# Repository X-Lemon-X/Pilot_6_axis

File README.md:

# 6 axis remote Controler
- Works over Wi-Fi ( sends constant length ASCI data frame)
- Up to 6 networks saved (with priority from  1 to 6)
- All settings of the Rc can be changed on a configuration website
- Controled inertia of the joysticks and signal values of the joystick coordinates
- Veriable signal refresh rate up to 200Hz
- Auto zero positioning (no more robots moving in slow speed without touching the pilot)
- USB-C charged!
- two 3-DOF joysticks
- 10 buttons (2 of which are on Joy Sticks)
- Integrated LCD
- The RC remembers settings so no need to set it up every time or reprogram it.

## The repo supports demo pc keyboard version of the RC 
 Pc keyboard version for RC without the need for the hardware.
 
 ```bash
  python3 -m venv .venv
  python3 -m pip -r requirements.txt
  source .venv/bin/activate
  python3 pilot_6axis/pilot_6axis/keyboard_rc.py -i IP_ADDRESS -p PORT -f FREQUENCY -v JOYSTICK_VALUE
 ```
for help
```bash
  python3 pilot_6axis/pilot_6axis/keyboard_rc.py
 ```

## To build and run ros package
```bash
  colcon build --packages-select pilot_6axis
  source install/setup.bash 
  ros2 run pilot_6axis rc_node
```

## Data frame
 Consist of 18 elements separated by ':'.
Depending on the settings int_Joystick_(left/right)_(MMin/MMax) value returned by joystick will vary. This setting values should be between -9999<=x<=9999 or 0<=x<=99999 or the data frame length won't be constant, for buttons: 1-pressed 0-not pressed.
```bash
 Example: "$Rc:  340:   200:   12:1:  500:-2045: 2045:1:1:1:0:1:1:0:1:0:#\r"
```

 1. control beginning "$Rc"
 2. joystick_left_x   (5-characters) 
 3. joystick_left_y   (5-characters)
 4. joystick_left_z   (5-characters)
 5. joystick_left_btn  (1-character)
 6. joystick_right_x   (5-characters)
 7. joystick_right_y   (5-characters)
 8. joystick_right_z   (5-characters)
 9. joystick_right_btn  (1-character)
 10. btn_1  (1-character)
 11. btn_2  (1-character)
 12. btn_3  (1-character)
 13. btn_4  (1-character)
 14. btn_5  (1-character)
 15. btn_6  (1-character)
 16. btn_7  (1-character)
 17. btn_8  (1-character)
 18. control end "#\r"

## How to use
### Setup
  1. Enable setup mode by pressing and holding the most centeral button 4 or 5 when turning the Rc On (doesn't matter which one).
  2. Connect to the Rc Wi-Fi network that is displayed on  the LCD.
  3. Open web browser and go to url displayed on the LCD.
  4. Set up the settings of the Rc and press save buttons on the bottom of the page. This will redirect you to the page where you will see if settings were saved. If you made some error it will be shown here.
  5. To leave setup mode shut down the Rc and turn it on again.
  6. Now the Rc will connect to the network with the highest priority that is available. If it can't connect to any of the saved networks it will keep trying to connect to them. If the Rc is connected to the network it will display the IP address on the LCD and show Connected status.
  7. Now setup is done and you can use the Rc.
## Settings list:
#### General Settings
  - **Joystick left MMin** -> minimum value of the left joystick x, y, z axis on the min of the range 
  - **Joystick left MMax** -> maximum value of the left joystick x, y, z axis on the max of the range
  - **Joystick left filer** -> inertia of the left joystick (0-1), the higher inertia the response of the joystick value will be faster.
  - **Joystick right MMin** -> minimum value of the right joystick x, y, z axis on the min of the range
  - **Joystick right MMax** -> maximum value of the right joystick x, y, z axis on the max of the range
  - **Joystick right filer** -> inertia of the right joystick (0-1)
  - **WIFI SSID** => SSID of the wifi network created by the RC in setup mode.
  - **WIFI PASSWORD** => password of the wifi network made by the RC in setup mode
  - **Update frequency** => frequency of sending data frame
  - **Target IP** => IP address to which the RC will send data frame
  - **Host Port** => port to which the RC will send data frame

#### WIFI target networks
  - **Wifi [number 1-6] : Seed** => SSID of the wifi network (where number means priority from 1 to 6)
  - **Wifi [number 1-6] : Password** => Password of the wifi network

## Required component list

### Component Images

  | Component | Photo | Component | Photo |
  |-----------|-------|-----------|-------|
  | PCB (order from JLCPCB) |  | Joystick 4-axis JH-D400B-M4 |  |
  | Toggle switch 6mm MTS-103 |  | Monostable switches 12mm PBS-33B |  |
  | Li-ion battery 3.7V 4000mAh |  | LCD 1.3" 128x64 OLED SSD1306 |  |
  | Antena 2.4GHz 3dBi WiFi RP-SMA |  | M3 6mm hex socket flat countersunk |  |
  | M3 heated insert M3xL3xOD4.2 |  | M3 5mm hex socket cylindrical |  |

### Component list 

  | Component Name                                   | Parts Count | Description                                              |
  |--------------------------------------------------|-------------|----------------------------------------------------------|
  | Joystick 4-axis JH-D400B-M4                      | 2           | 3-DOF joysticks for axis control                        |
  | Toggle switch 6mm MTS-103                        | 1           | Main toggle switch for power or mode selection           |
  | Monostable switches 12mm PBS-33B                 | 8           | Momentary push buttons for user input                   |
  | Li-ion battery 606090 3.7V 4000mAh               | 1           | Rechargeable battery for power supply                    |
  | LCD 1.3" 128x64 OLED SSD1306                     | 1           | Display for status and configuration                     |
  | Antena 2.4GHz 3dB WiFi 2.4GHz RP-SMA             | 1           | External Wi-Fi antenna for wireless communication        |
  | M3 6mm hex socket flat countersunk screws        | 14          | Screws for assembling the enclosure                      |
  | M3 heated insert M3xL3xOD4.2                     | 19          | Threaded inserts for secure screw mounting               |
  | M3 5mm hex socket cylindrical screws             | 4           | Additional screws for assembly                           |
  | PCB (order from JLCPCB)                          | 1           | Main circuit board for the controller                    |
  | BOM Components (see BOM file)                    | -           | All other electronic components (resistors, ICs, etc.)   |

- BOM file "Electric schematic/Pilot6Axis/jlcpcb/production_files/BOM-Pilot6Axis.csv"
- JLCB gerber files "Electric schematic/Pilot6Axis/jlcpcb/production_files/GERBER-Pilot6Axis.zip"

## How to assembly
  You figure it out.

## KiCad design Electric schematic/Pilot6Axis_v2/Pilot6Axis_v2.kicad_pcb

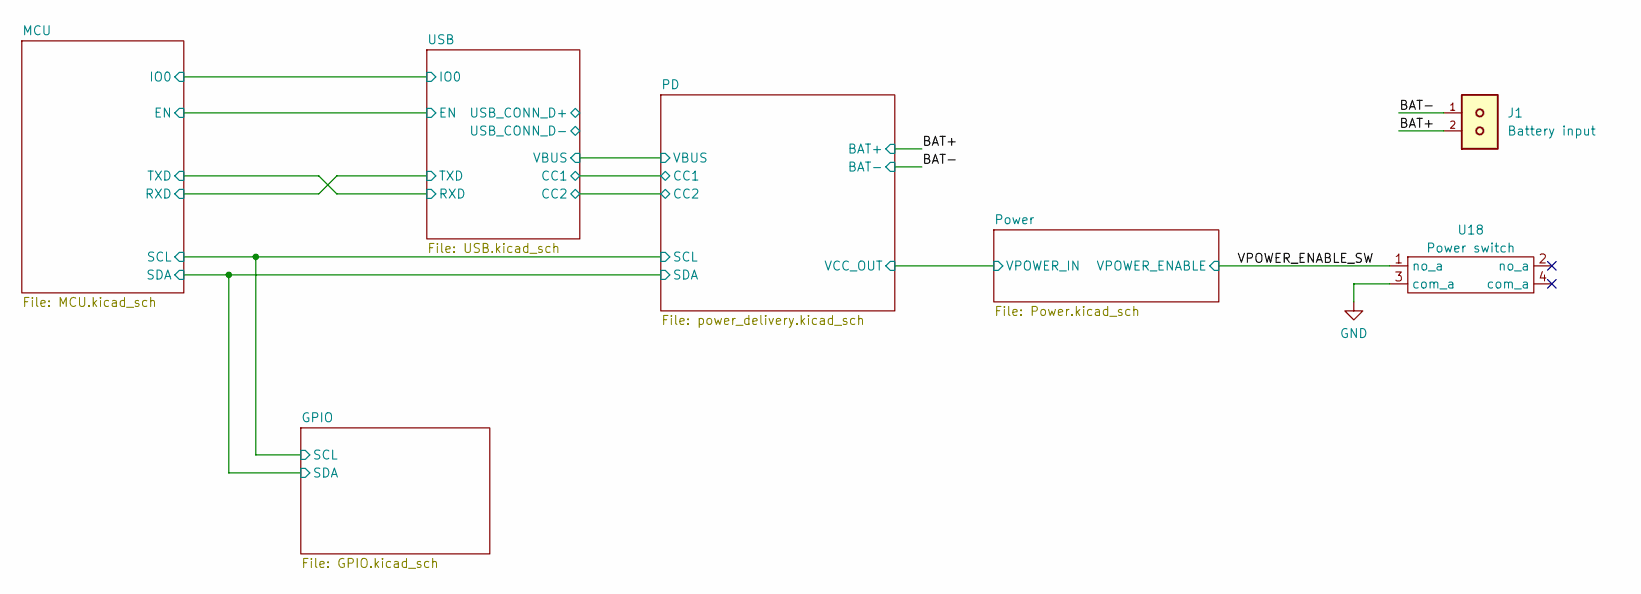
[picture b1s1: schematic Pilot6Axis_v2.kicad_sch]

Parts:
J1: Battery input; JST_PH_B2B-PH-K_1x02_P2.00mm_Vertical
U18: Power switch; ts-1212f

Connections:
/BAT+: J1.2; also elsewhere on the board
/VPOWER_ENABLE_SW: U18.1 (no_a); also elsewhere on the board
GND: J1.1, U18.3 (com_a); also elsewhere on the board

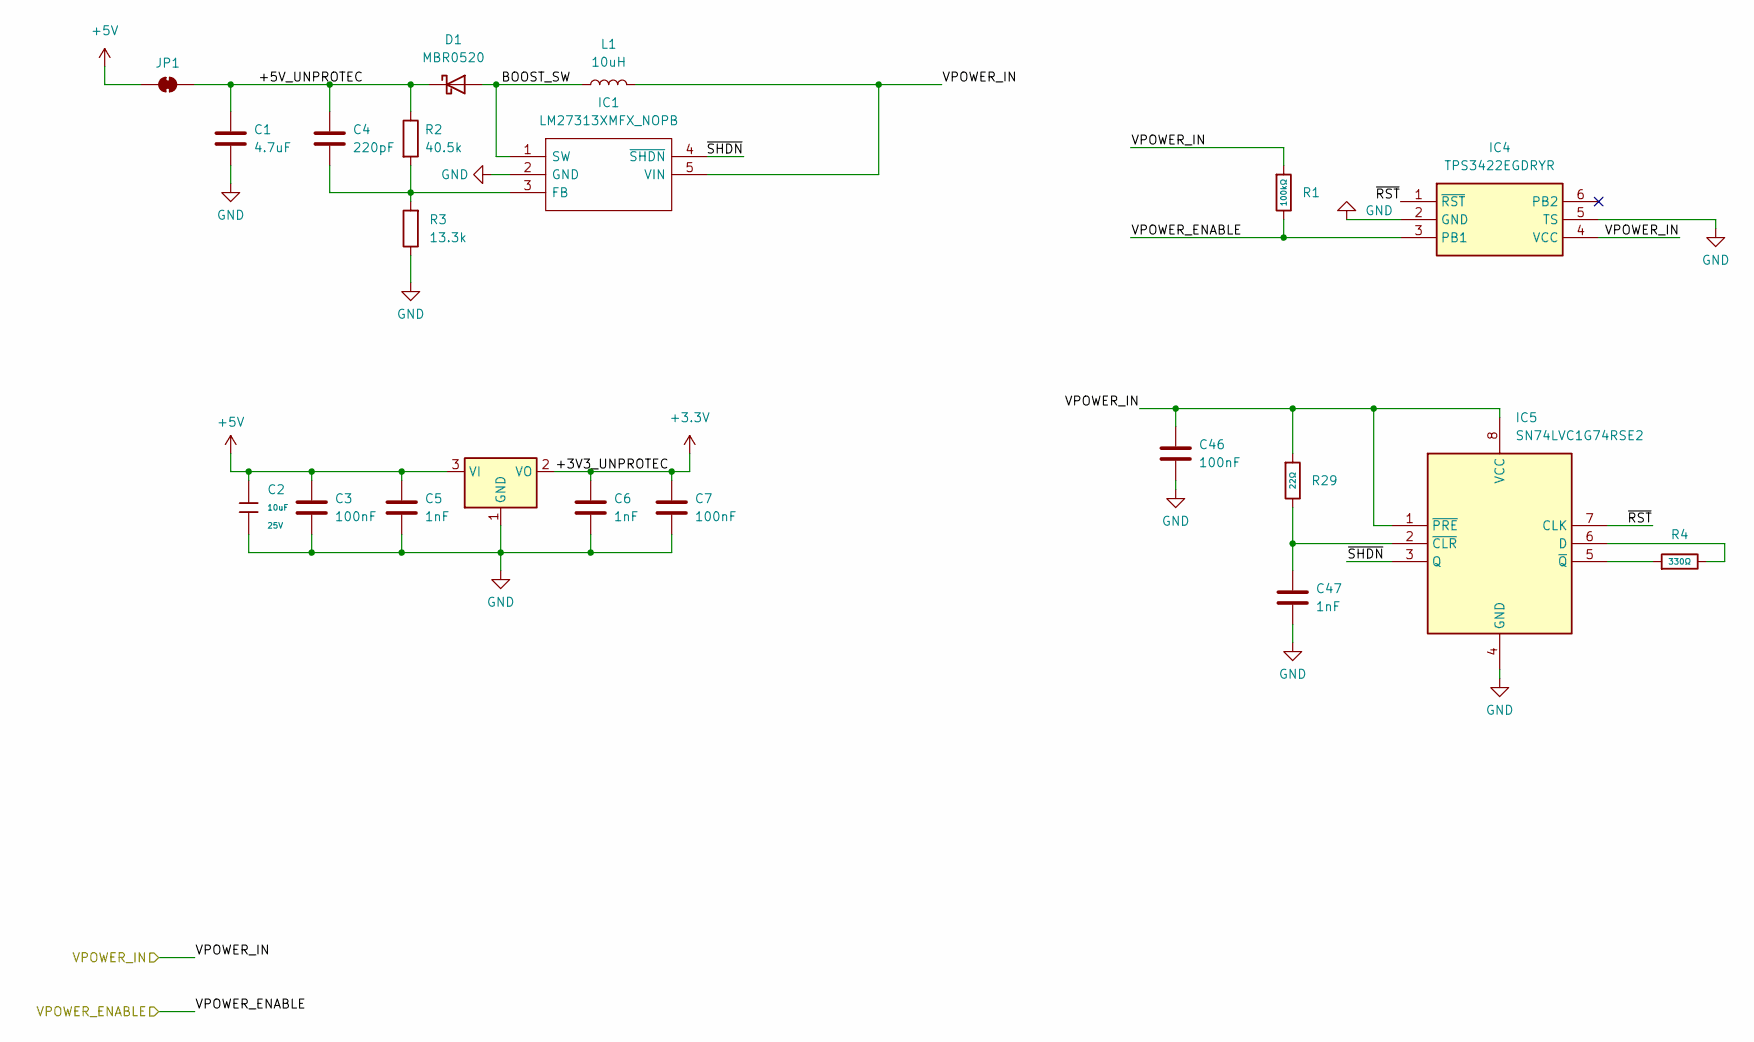
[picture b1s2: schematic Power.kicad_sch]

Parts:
C1: 4.7uF; C_0603_1608Metric; LCSC C19666
C2: 10uF; C_0603; Voltage Rated 25V; Tolerance ±20%; Part CL10A106MA8NRNC; LCSC C96446
C3, C7, C46: 100nF; C_0603_1608Metric; LCSC C14663
C4: 220pF; C_0603_1608Metric; LCSC C1603
C5, C6, C47: 1nF; C_0603_1608Metric; LCSC C1588
D1: MBR0520; D_0603_1608Metric; LCSC C2858712
IC1: LM27313XMFX_NOPB; SOT-23-5; Manufacturer_Part_Number LM27313XMFX/NOPB; Mouser Part Number 926-LM27313XMFX/NOPB
IC4: TPS3422EGDRYR; DRY_R-PUSON-N6_; Manufacturer_Part_Number TPS3422EGDRYR; Mouser Part Number 595-TPS3422EGDRYR
IC5: SN74LVC1G74RSE2; Manufacturer_Part_Number SN74LVC1G74RSE2; Mouser Part Number 595-SN74LVC1G74RSE2
JP1: SolderJumper_2_Bridged; SolderJumper-2_P1.3mm_Open_TrianglePad1.0x1.5mm
L1: 10uH; L_Cenker_CKCS4018; LCSC C1035
R1: 100kΩ; R_0603; Overload Voltage (Max) 75V; Tolerance ±1%; Part 0603WAF1003T5E; LCSC C25803
R2: 40.5k; R_0603_1608Metric; LCSC C12447
R3: 13.3k; R_0603_1608Metric; LCSC C25952
R4: 330Ω; R_0603; Overload Voltage (Max) 75V; Tolerance ±1%; Part 0603WAF3300T5E; LCSC C23138
R29: 22Ω; R_0603; Overload Voltage (Max) 75V; Tolerance ±1%; Part 0603WAF220JT5E; LCSC C23345
U1: AMS1117-3.3; SOT-223-3_TabPin2; LCSC C6186

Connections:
+3.3V: C6.1, C7.1, U1.2 (VO); also elsewhere on the board
+5V: C2.1, C3.1, C5.1, JP1.1 (A), U1.3 (VI); also elsewhere on the board
/PD/VCC_OUT: C46.1, IC1.5 (VIN), IC4.4 (VCC), IC5.1 (~PRE), IC5.8 (VCC), L1.2, R1.1, R29.1; also elsewhere on the board
/Power/+5V_UNPROTEC: C1.1, C4.2, D1.1 (K), JP1.2 (B), R2.1
/Power/BOOST_SW: D1.2 (A), IC1.1 (SW), L1.1
/Power/~RST: IC4.1 (~RST), IC5.7 (CLK)
/Power/~SHDN: IC1.4 (~SHDN), IC5.3 (Q)
/VPOWER_ENABLE_SW: IC4.3 (PB1), R1.2; also elsewhere on the board
GND: C1.2, C2.2, C3.2, C5.2, C6.2, C7.2, C46.2, C47.2, IC1.2 (GND), IC4.2 (GND), IC4.5 (TS), IC5.4 (GND), R3.1, U1.1 (GND); also elsewhere on the board
unnamed: C4.1, IC1.3 (FB), R2.2, R3.2
unnamed: IC5.6 (D), R4.2
unnamed: C47.1, IC5.2 (~CLR), R29.2
unnamed: IC5.5 (~Q), R4.1

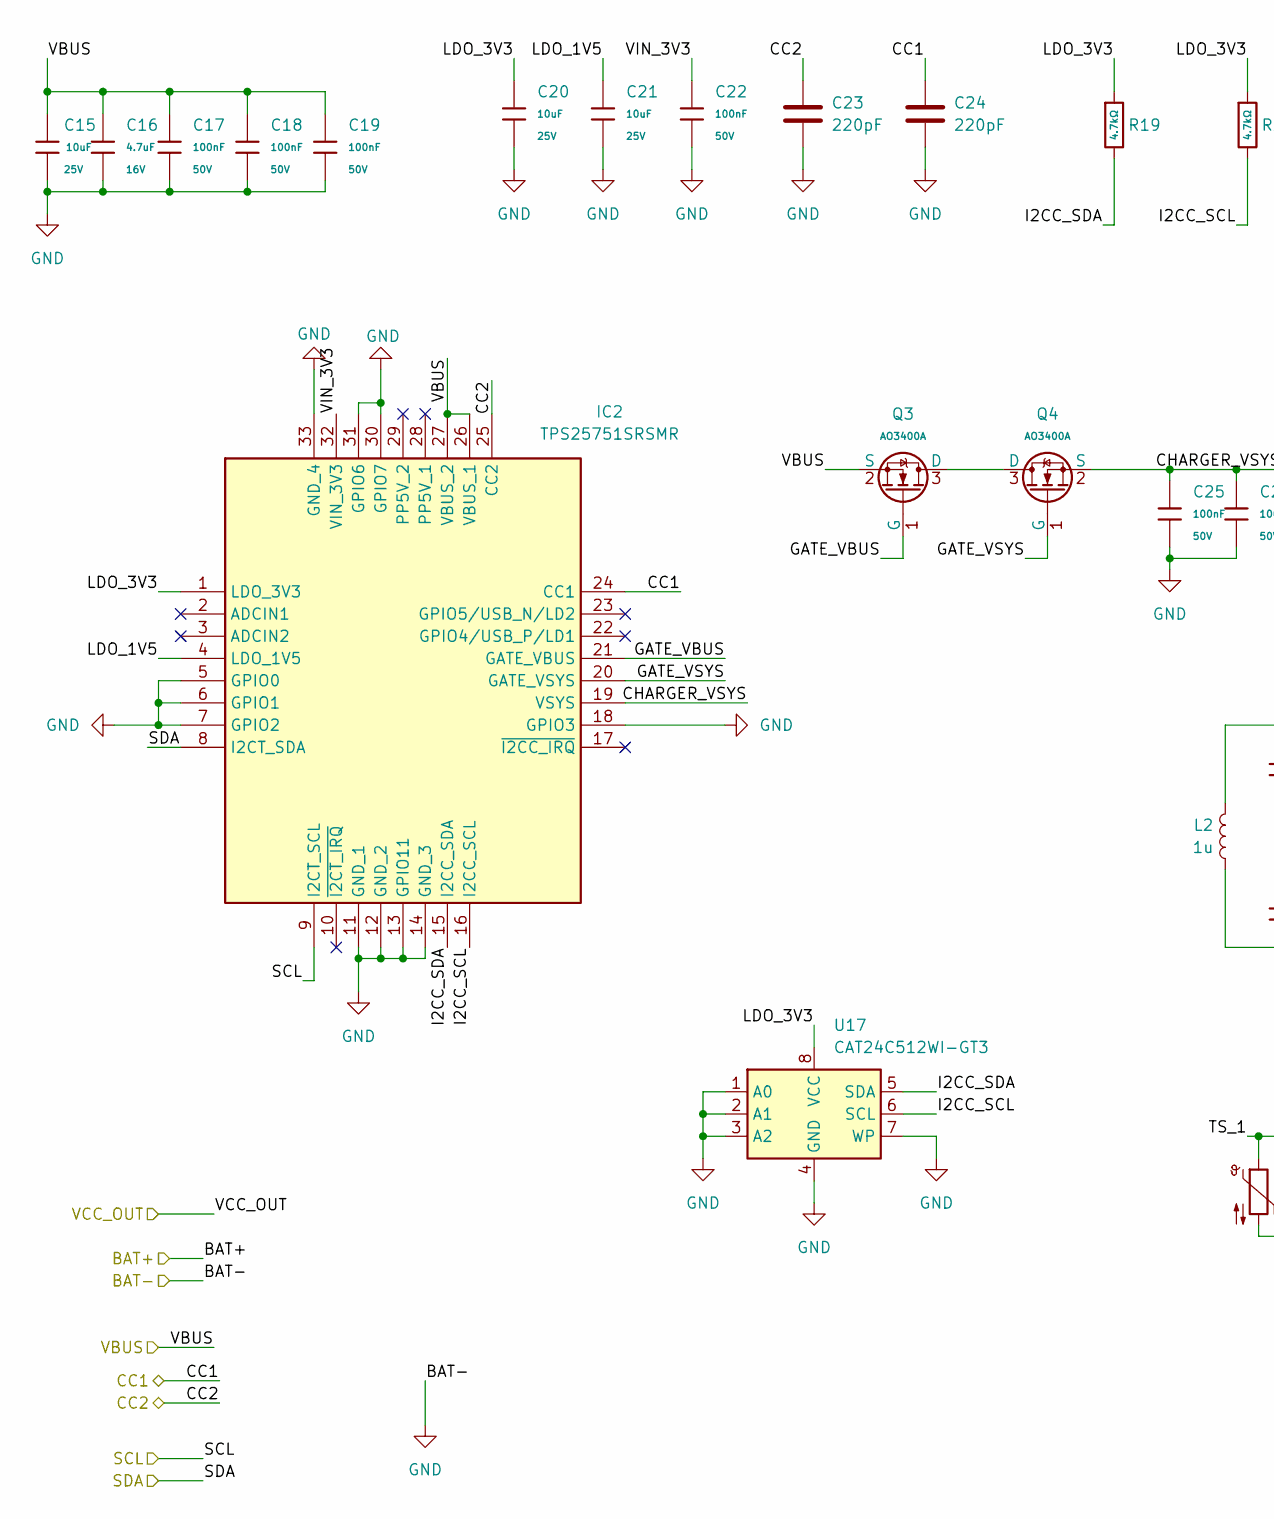
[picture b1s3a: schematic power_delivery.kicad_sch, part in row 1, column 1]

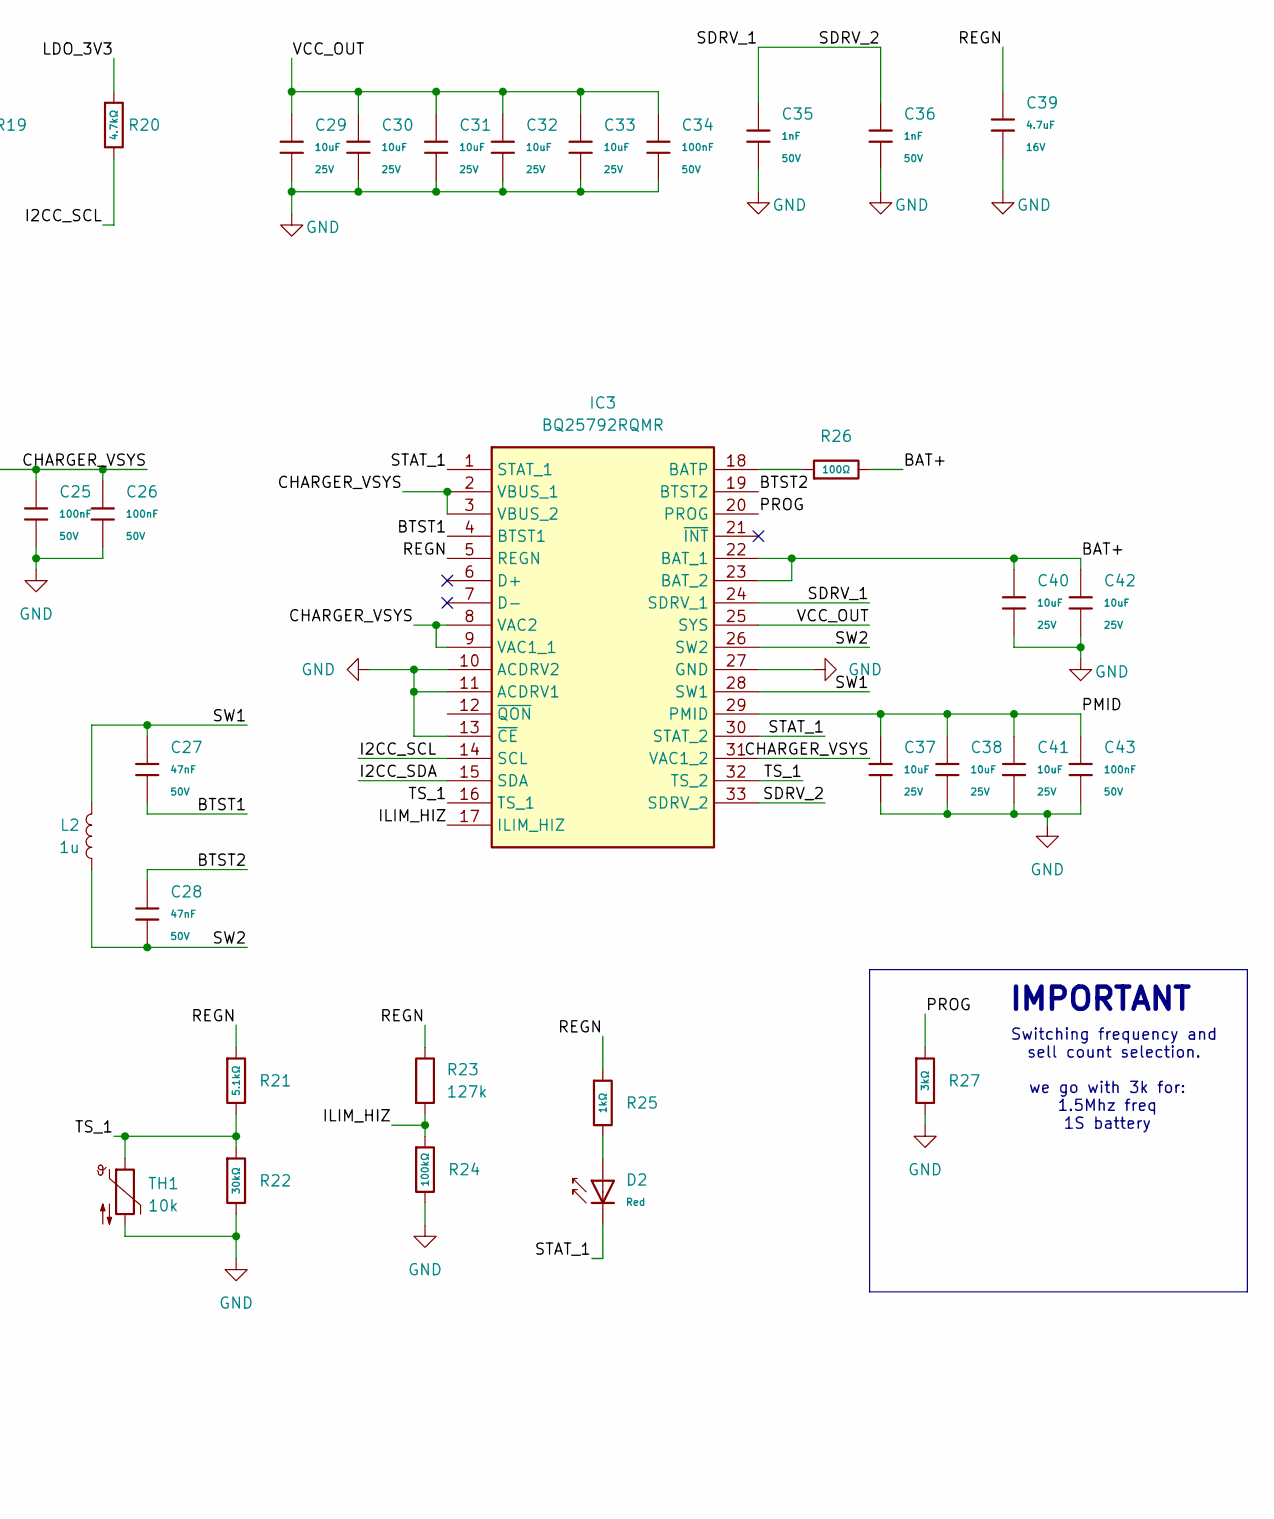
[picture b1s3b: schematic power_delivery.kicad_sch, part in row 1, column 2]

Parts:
C15, C20, C21, C29, C30, C31, C32, C33, C37, C38, C40, C41, C42: 10uF; C_0603; Voltage Rated 25V; Tolerance ±20%; Part CL10A106MA8NRNC; LCSC C96446
C16, C39: 4.7uF; C_0603; Voltage Rated 16V; Tolerance ±10%; Part CL10A475KO8NNNC; LCSC C19666
C17, C18, C19, C22, C25, C26, C34, C43: 100nF; C_0603; Voltage Rated 50V; Tolerance ±10%; Part CC0603KRX7R9BB104; LCSC C14663
C23, C24: 220pF; C_0603_1608Metric; LCSC C1603
C27, C28: 47nF; C_0603; Voltage Rated 50V; Tolerance ±10%; Part CL10B473KB8NNNC; LCSC C1622
C35, C36: 1nF; C_0603; Voltage Rated 50V; Tolerance ±10%; Part CL10B102KB8NNNC; LCSC C1588
D2: Red; D_0603; Part KT-0603R; LCSC C2286
IC2: TPS25751SRSMR; QFN40P400X400X100-33N-D; Manufacturer_Part_Number TPS25751SRSMR; Mouser Part Number 595-TPS25751SRSMR
IC3: BQ25792RQMR; Manufacturer_Part_Number BQ25792RQMR; Mouser Part Number 595-BQ25792RQMR
L2: 1u; L_APV_APH0420
Q3, Q4: AO3400A; Q_SOT-23; Part AO3400A; LCSC C20917
R19, R20: 4.7kΩ; R_0603; Overload Voltage (Max) 75V; Tolerance ±1%; Part 0603WAF4701T5E; LCSC C23162
R21: 5.1kΩ; R_0402; Overload Voltage (Max) 50V; Tolerance ±1%; Part 0402WGF5101TCE; LCSC C25905
R22: 30kΩ; R_0603; Overload Voltage (Max) 75V; Tolerance ±1%; Part 0603WAF3002T5E; LCSC C22984
R23: 127k; R_0603_1608Metric
R24: 100kΩ; R_0603; Overload Voltage (Max) 75V; Tolerance ±1%; Part 0603WAF1003T5E; LCSC C25803
R25: 1kΩ; R_0603; Overload Voltage (Max) 75V; Tolerance ±1%; Part 0603WAF1001T5E; LCSC C21190
R26: 100Ω; R_0603; Overload Voltage (Max) 75V; Tolerance ±1%; Part 0603WAF1000T5E; LCSC C22775
R27: 3kΩ; R_0603; Overload Voltage (Max) 75V; Tolerance ±1%; Part 0603WAF3001T5E; LCSC C4211
TH1: 10k; PinHeader_1x02_P2.54mm_Vertical
U17: CAT24C512WI-GT3; SOIC-8_3.9x4.9mm_P1.27mm

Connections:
/BAT+: C40.1, C42.1, IC3.22 (BAT_1), IC3.23 (BAT_2), R26.2; also elsewhere on the board
/GPIO/SCL: IC2.9 (I2CT_SCL); also elsewhere on the board
/GPIO/SDA: IC2.8 (I2CT_SDA); also elsewhere on the board
/PD/BTST1: C27.2, IC3.4 (BTST1)
/PD/BTST2: C28.1, IC3.19 (BTST2)
/PD/CC1: C24.2, IC2.24 (CC1); also elsewhere on the board
/PD/CC2: C23.2, IC2.25 (CC2); also elsewhere on the board
/PD/CHARGER_VSYS: C25.1, C26.1, IC2.19 (VSYS), IC3.2 (VBUS_1), IC3.3 (VBUS_2), IC3.8 (VAC2), IC3.9 (VAC1_1), IC3.31 (VAC1_2), Q4.2 (S)
/PD/GATE_VBUS: IC2.21 (GATE_VBUS), Q3.1 (G)
/PD/GATE_VSYS: IC2.20 (GATE_VSYS), Q4.1 (G)
/PD/I2CC_SCL: IC2.16 (I2CC_SCL), IC3.14 (SCL), R20.2, U17.6 (SCL)
/PD/I2CC_SDA: IC2.15 (I2CC_SDA), IC3.15 (SDA), R19.2, U17.5 (SDA)
/PD/ILIM_HIZ: IC3.17 (ILIM_HIZ), R23.2, R24.1
/PD/LDO_1V5: C21.1, IC2.4 (LDO_1V5)
/PD/LDO_3V3: C20.1, IC2.1 (LDO_3V3), R19.1, R20.1, U17.8 (VCC)
/PD/PMID: C37.1, C38.1, C41.1, C43.1, IC3.29 (PMID)
/PD/PROG: IC3.20 (PROG), R27.1
/PD/REGN: C39.1, IC3.5 (REGN), R21.1, R23.1, R25.1
/PD/SDRV_1: C35.1, C36.1, IC3.24 (SDRV_1), IC3.33 (SDRV_2)
/PD/STAT_1: D2.1, IC3.1 (STAT_1), IC3.30 (STAT_2)
/PD/SW1: C27.1, IC3.28 (SW1), L2.1
/PD/SW2: C28.2, IC3.26 (SW2), L2.2
/PD/TS_1: IC3.16 (TS_1), IC3.32 (TS_2), R21.2, R22.1, TH1.1
/PD/VBUS: C15.1, C16.1, C17.1, C18.1, C19.1, IC2.26 (VBUS_1), IC2.27 (VBUS_2), Q3.2 (S); also elsewhere on the board
/PD/VCC_OUT: C29.1, C30.1, C31.1, C32.1, C33.1, C34.1, IC3.25 (SYS); also elsewhere on the board
/PD/VIN_3V3: C22.1, IC2.32 (VIN_3V3)
GND: C15.2, C16.2, C17.2, C18.2, C19.2, C20.2, C21.2, C22.2, C23.1, C24.1, C25.2, C26.2, C29.2, C30.2, C31.2, C32.2, C33.2, C34.2, C35.2, C36.2, C37.2, C38.2, C39.2, C40.2, C41.2, C42.2, C43.2, IC2.5 (GPIO0), IC2.6 (GPIO1), IC2.7 (GPIO2), IC2.11 (GND_1), IC2.12 (GND_2), IC2.13 (GPIO11), IC2.14 (GND_3), IC2.18 (GPIO3), IC2.30 (GPIO7), IC2.31 (GPIO6), IC2.33 (GND_4), IC3.10 (ACDRV2), IC3.11 (ACDRV1), IC3.13 (~CE), IC3.27 (GND), R22.2, R24.2, R27.2, TH1.2, U17.1 (A0), U17.2 (A1), U17.3 (A2), U17.4 (GND), U17.7 (WP); also elsewhere on the board
unnamed: D2.2, R25.2
unnamed: IC3.18 (BATP), R26.1
unnamed: Q3.3 (D), Q4.3 (D)

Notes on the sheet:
Switching frequency and sell count selection.
we go with 3k for: 1.5Mhz freq 1S battery
IMPORTANT

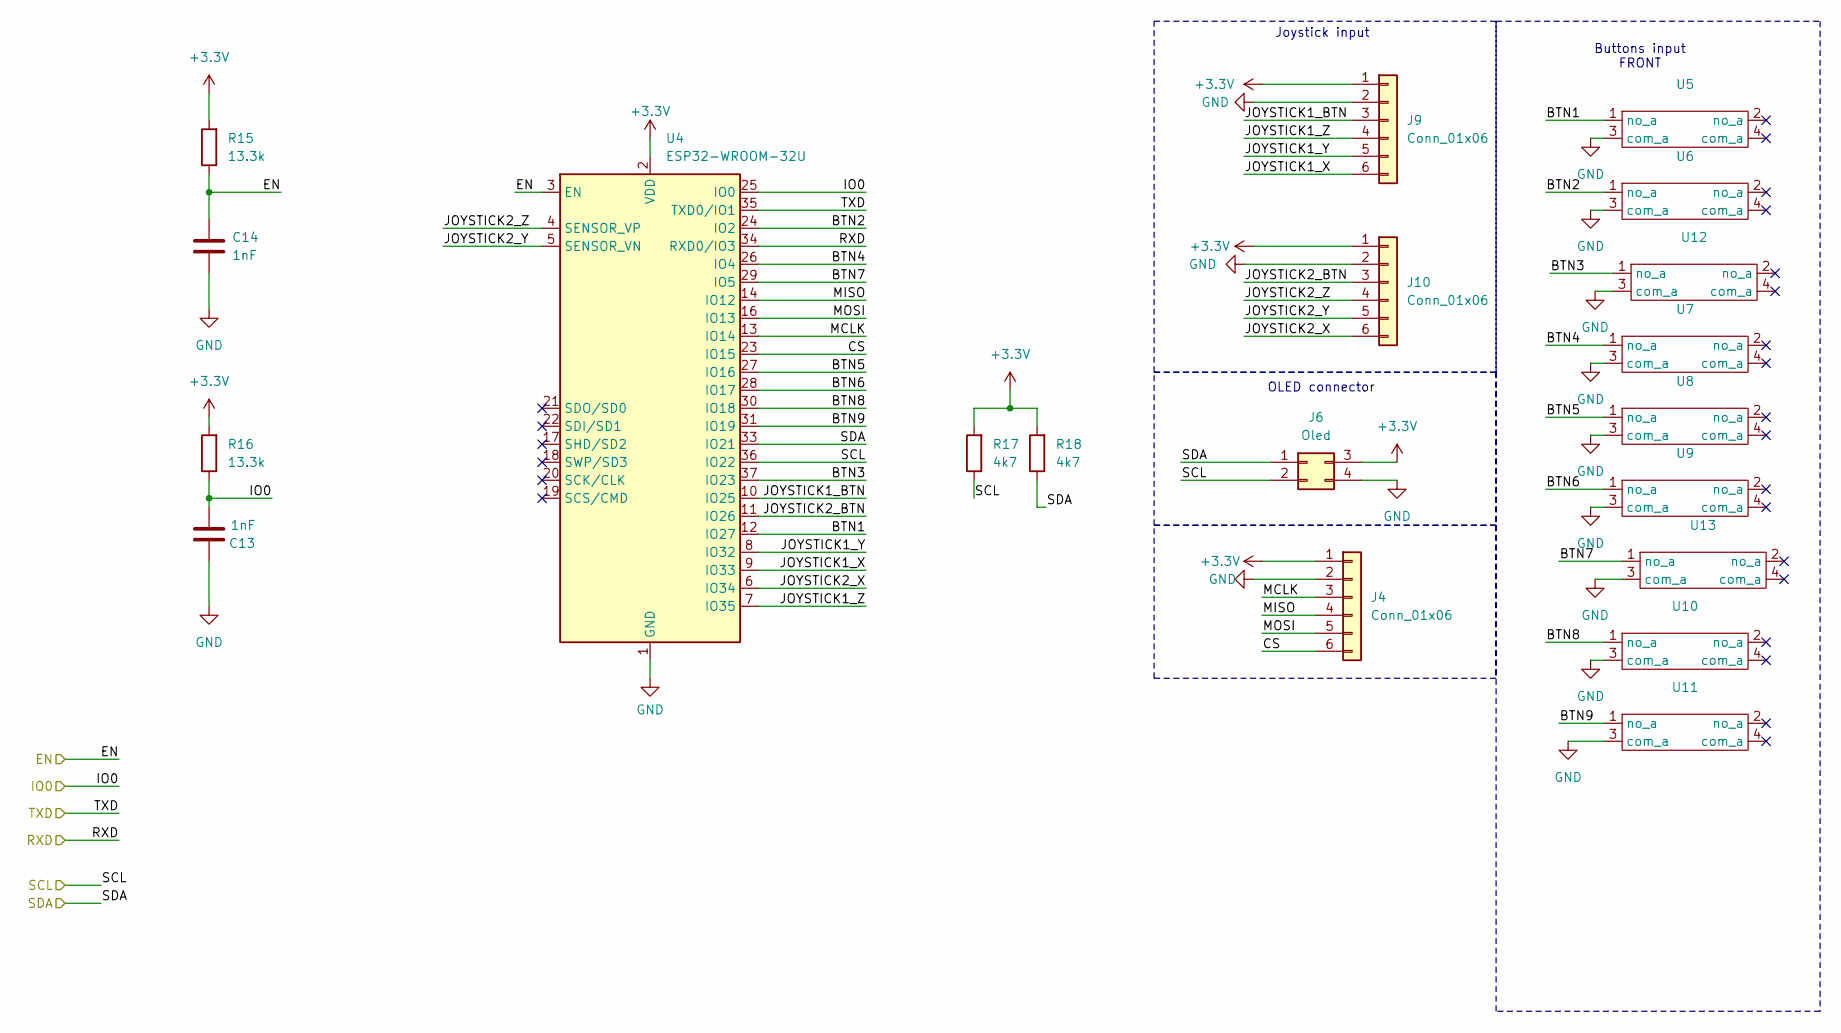
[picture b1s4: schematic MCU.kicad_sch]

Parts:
C13, C14: 1nF; C_0603_1608Metric; LCSC C1588
J4, J9, J10: Conn_01x06; JST_PH_B6B-PH-K_1x06_P2.00mm_Vertical
J6: Oled; PinSocket_2x02_P2.54mm_Vertical
R15, R16: 13.3k; R_0603_1608Metric; LCSC C25952
R17, R18: 4k7; R_0402_1005Metric; LCSC C25952
U4: ESP32-WROOM-32U
U5, U6, U7, U8, U9, U10, U11, U12, U13: ts-1212f

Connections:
+3.3V: J4.1, J6.3, J9.1, J10.1, R15.2, R16.2, R17.2, R18.2, U4.2 (VDD); also elsewhere on the board
/GPIO/SCL: J6.2, R17.1, U4.36 (IO22); also elsewhere on the board
/GPIO/SDA: J6.1, R18.1, U4.33 (IO21); also elsewhere on the board
/MCU/BTN1: U4.12 (IO27), U5.1 (no_a)
/MCU/BTN2: U4.24 (IO2), U6.1 (no_a)
/MCU/BTN3: U4.37 (IO23), U12.1 (no_a)
/MCU/BTN4: U4.26 (IO4), U7.1 (no_a)
/MCU/BTN5: U4.27 (IO16), U8.1 (no_a)
/MCU/BTN6: U4.28 (IO17), U9.1 (no_a)
/MCU/BTN7: U4.29 (IO5), U13.1 (no_a)
/MCU/BTN8: U4.30 (IO18), U10.1 (no_a)
/MCU/BTN9: U4.31 (IO19), U11.1 (no_a)
/MCU/CS: J4.6, U4.23 (IO15)
/MCU/EN: C14.1, R15.1, U4.3 (EN); also elsewhere on the board
/MCU/IO0: C13.2, R16.1, U4.25 (IO0); also elsewhere on the board
/MCU/JOYSTICK1_BTN: J9.3, U4.10 (IO25)
/MCU/JOYSTICK1_X: J9.6, U4.9 (IO33)
/MCU/JOYSTICK1_Y: J9.5, U4.8 (IO32)
/MCU/JOYSTICK1_Z: J9.4, U4.7 (IO35)
/MCU/JOYSTICK2_BTN: J10.3, U4.11 (IO26)
/MCU/JOYSTICK2_X: J10.6, U4.6 (IO34)
/MCU/JOYSTICK2_Y: J10.5, U4.5 (SENSOR_VN)
/MCU/JOYSTICK2_Z: J10.4, U4.4 (SENSOR_VP)
/MCU/MCLK: J4.3, U4.13 (IO14)
/MCU/MISO: J4.4, U4.14 (IO12)
/MCU/MOSI: J4.5, U4.16 (IO13)
/MCU/RXD: U4.34 (RXD0/IO3); also elsewhere on the board
/MCU/TXD: U4.35 (TXD0/IO1); also elsewhere on the board
GND: C13.1, C14.2, J4.2, J6.4, J9.2, J10.2, U4.1 (GND), U4.15 (GND), U4.38 (GND), U4.39 (GND), U5.3 (com_a), U6.3 (com_a), U7.3 (com_a), U8.3 (com_a), U9.3 (com_a), U10.3 (com_a), U11.3 (com_a), U12.3 (com_a), U13.3 (com_a); also elsewhere on the board

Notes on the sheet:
Buttons input FRONT
Joystick input
OLED connector

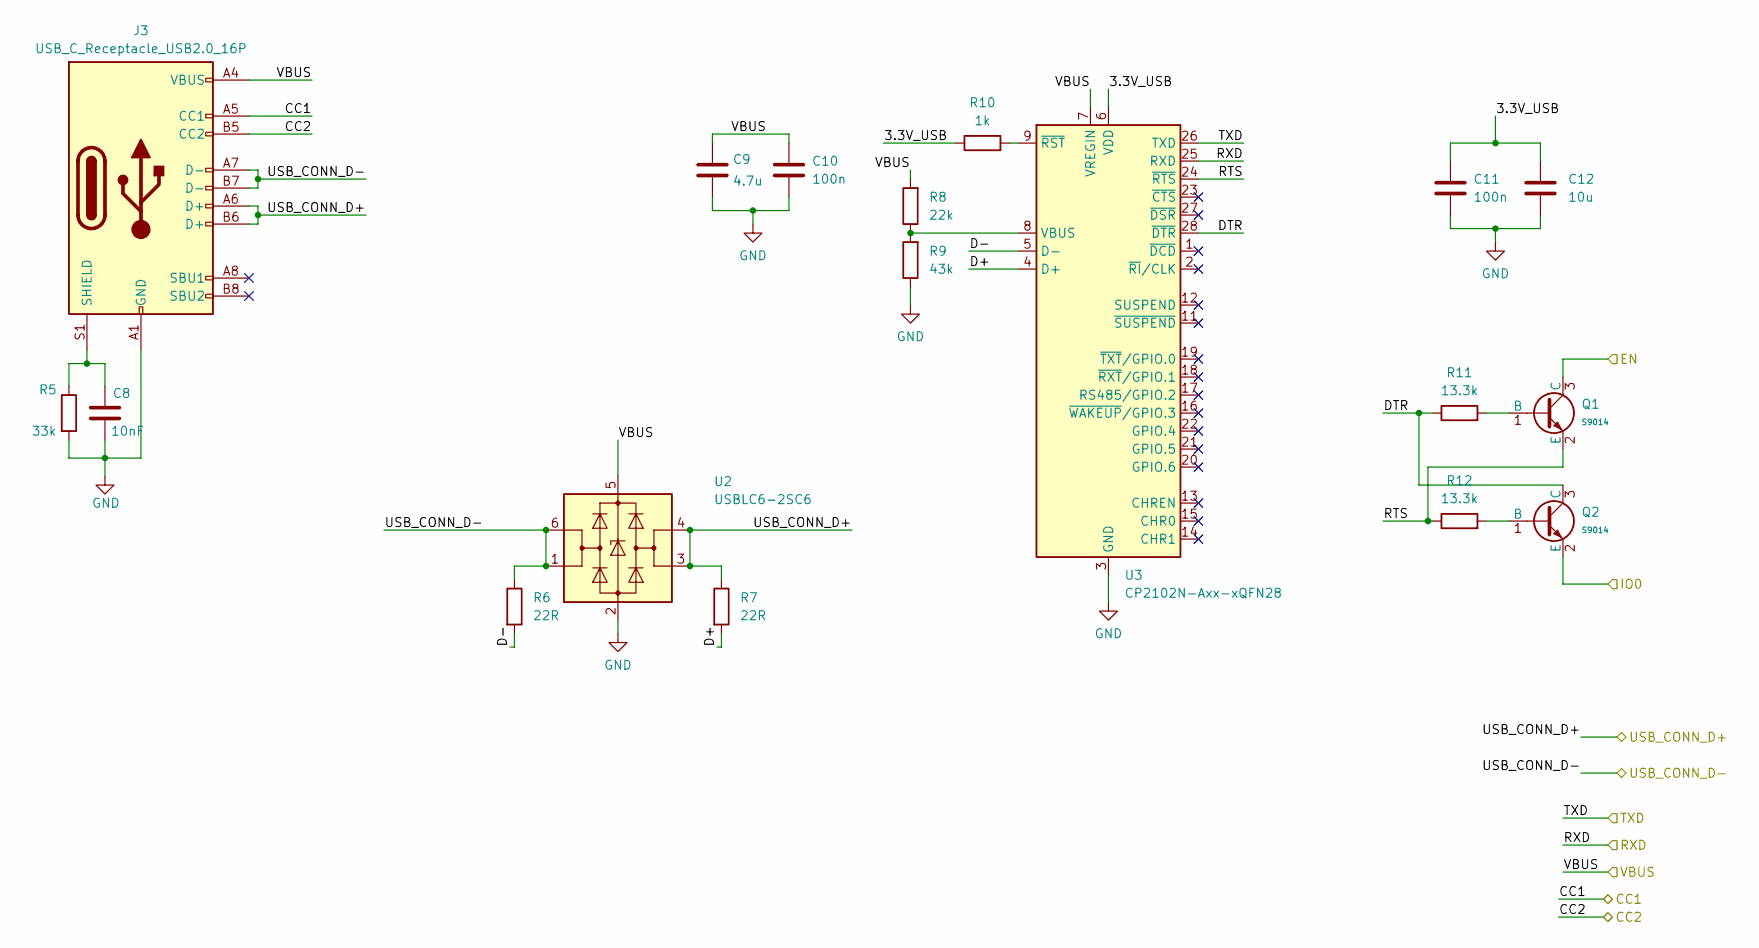
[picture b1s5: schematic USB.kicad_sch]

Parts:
C8: 10nF; R_0603_1608Metric; LCSC C57112
C9: 4.7u; R_0603_1608Metric; LCSC C19702
C10, C11: 100n; R_0603_1608Metric; LCSC C14663
C12: 10u; R_0603_1608Metric; LCSC C19702
J3: USB_C_Receptacle_USB2.0_16P; USB_C_Receptacle_HCTL_HC-TYPE-C-16P-01A; LCSC C2765186
Q1, Q2: S9014; Q_SOT-23; Part S9014; LCSC C20069130
R5: 33k; R_0603_1608Metric; LCSC C4216
R6, R7: 22R; R_0603_1608Metric; LCSC C71618
R8: 22k; R_0402_1005Metric; LCSC C25952
R9: 43k; R_0402_1005Metric; LCSC C25952
R10: 1k; R_0603_1608Metric; LCSC C14676
R11, R12: 13.3k; R_0603_1608Metric; LCSC C25952
U2: USBLC6-2SC6; SOT-23-6; LCSC C5180249
U3: CP2102N-Axx-xQFN28; QFN-28-1EP_5x5mm_P0.5mm_EP3.35x3.35mm; LCSC C964632

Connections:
/MCU/EN: Q1.3 (C); also elsewhere on the board
/MCU/IO0: Q2.2 (E); also elsewhere on the board
/MCU/RXD: U3.26 (TXD); also elsewhere on the board
/MCU/TXD: U3.25 (RXD); also elsewhere on the board
/PD/CC1: J3.A5 (CC1); also elsewhere on the board
/PD/CC2: J3.B5 (CC2); also elsewhere on the board
/PD/VBUS: C9.1, C10.1, J3.A4 (VBUS), J3.A9 (VBUS), J3.B4 (VBUS), J3.B9 (VBUS), R8.2, U2.5 (VBUS), U3.7 (VREGIN); also elsewhere on the board
/USB/3.3V_USB: C11.1, C12.1, R10.1, U3.6 (VDD)
/USB/D+: R7.2, U3.4 (D+)
/USB/D-: R6.2, U3.5 (D-)
/USB/DTR: Q2.3 (C), R11.1, U3.28 (~DTR)
/USB/RTS: Q1.2 (E), R12.1, U3.24 (~RTS)
/USB/USB_CONN_D+: J3.A6 (D+), J3.B6 (D+), R7.1, U2.3 (I/O2), U2.4 (I/O2)
/USB/USB_CONN_D-: J3.A7 (D-), J3.B7 (D-), R6.1, U2.1 (I/O1), U2.6 (I/O1)
GND: C8.2, C9.2, C10.2, C11.2, C12.2, J3.A1 (GND), J3.A12 (GND), J3.B1 (GND), J3.B12 (GND), R5.2, R9.1, U2.2 (GND), U3.3 (GND), U3.29 (GND); also elsewhere on the board
unnamed: C8.1, J3.S1 (SHIELD), R5.1
unnamed: Q1.1 (B), R11.2
unnamed: Q2.1 (B), R12.2
unnamed: R8.1, R9.2, U3.8 (VBUS)
unnamed: R10.2, U3.9 (~RST)

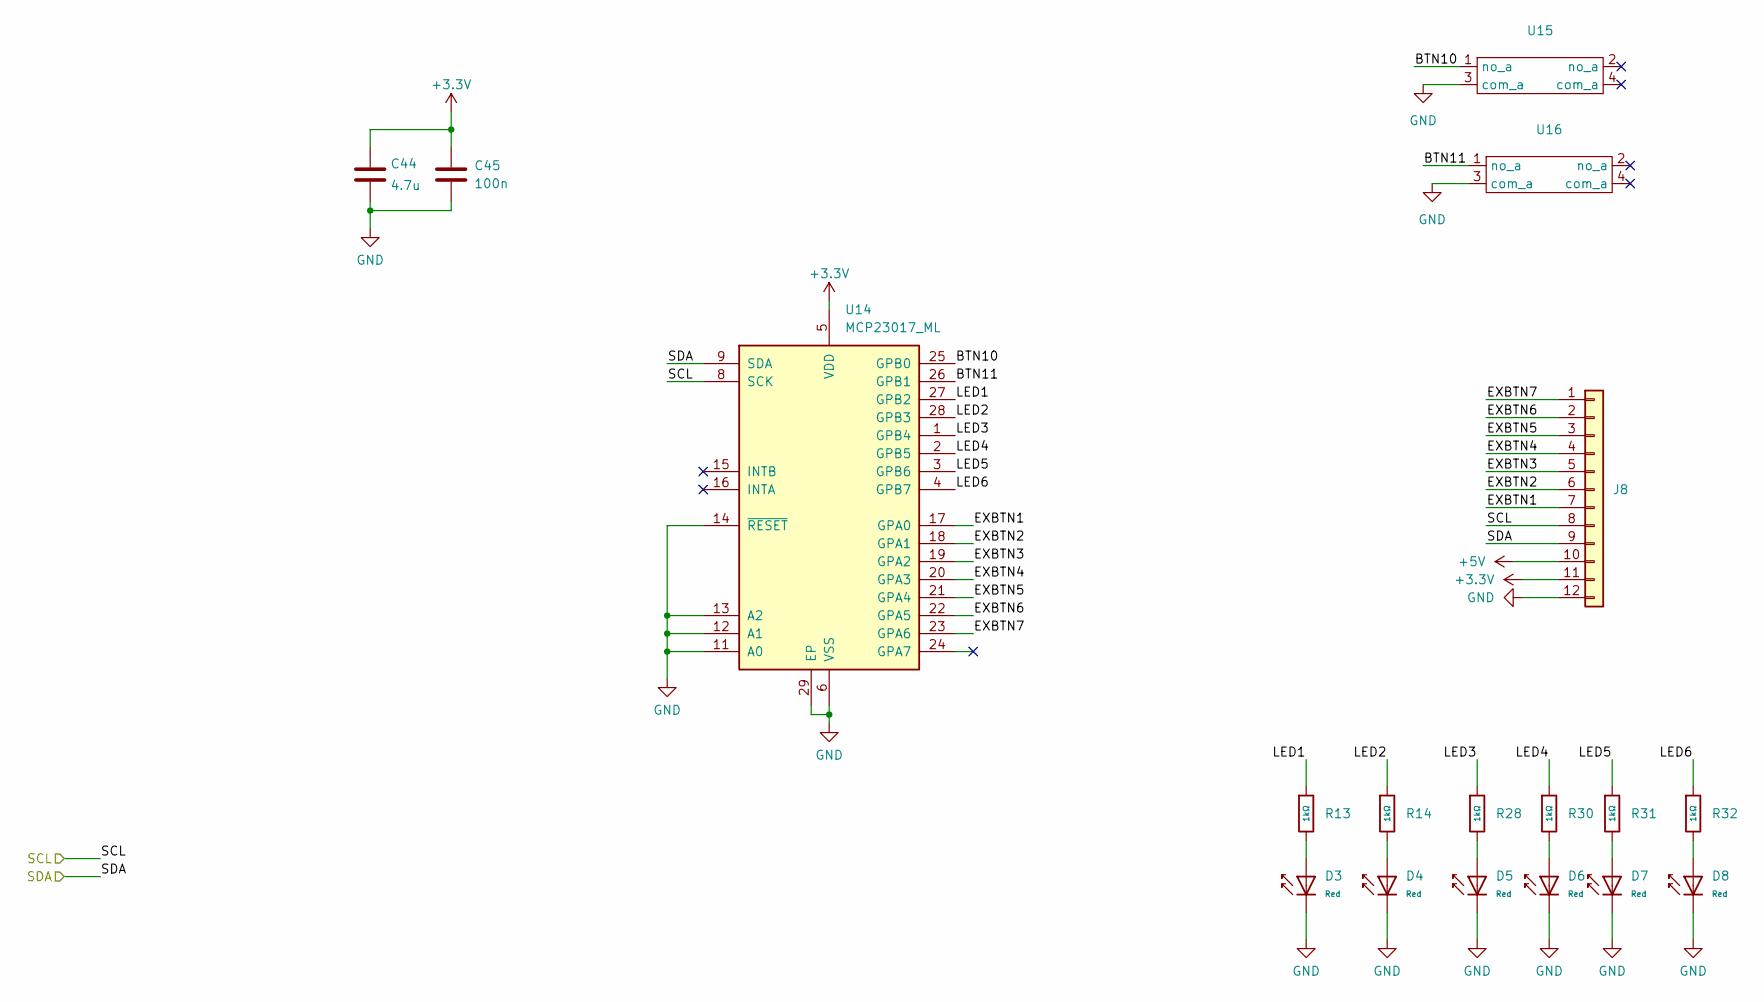
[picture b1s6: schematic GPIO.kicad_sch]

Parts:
C44: 4.7u; R_0603_1608Metric; LCSC C19702
C45: 100n; R_0603_1608Metric; LCSC C14663
D3, D4, D5, D6, D7, D8: Red; D_0603; Part KT-0603R; LCSC C2286
J8: Conn_01x12; JST_PH_B12B-PH-K_1x12_P2.00mm_Vertical
R13, R14, R28, R30, R31, R32: 1kΩ; R_0603; Overload Voltage (Max) 75V; Tolerance ±1%; Part 0603WAF1001T5E; LCSC C21190
U14: MCP23017_ML; QFN-28-1EP_6x6mm_P0.65mm_EP4.25x4.25mm
U15, U16: ts-1212f

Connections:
+3.3V: C44.1, C45.1, J8.11, U14.5 (VDD); also elsewhere on the board
+5V: J8.10; also elsewhere on the board
/GPIO/BTN10: U14.25 (GPB0), U15.1 (no_a)
/GPIO/BTN11: U14.26 (GPB1), U16.1 (no_a)
/GPIO/EXBTN1: J8.7, U14.17 (GPA0)
/GPIO/EXBTN2: J8.6, U14.18 (GPA1)
/GPIO/EXBTN3: J8.5, U14.19 (GPA2)
/GPIO/EXBTN4: J8.4, U14.20 (GPA3)
/GPIO/EXBTN5: J8.3, U14.21 (GPA4)
/GPIO/EXBTN6: J8.2, U14.22 (GPA5)
/GPIO/EXBTN7: J8.1, U14.23 (GPA6)
/GPIO/LED1: R13.1, U14.27 (GPB2)
/GPIO/LED2: R14.1, U14.28 (GPB3)
/GPIO/LED3: R28.1, U14.1 (GPB4)
/GPIO/LED4: R30.1, U14.2 (GPB5)
/GPIO/LED5: R31.1, U14.3 (GPB6)
/GPIO/LED6: R32.1, U14.4 (GPB7)
/GPIO/SCL: J8.8, U14.8 (SCK); also elsewhere on the board
/GPIO/SDA: J8.9, U14.9 (SDA); also elsewhere on the board
GND: C44.2, C45.2, D3.1, D4.1, D5.1, D6.1, D7.1, D8.1, J8.12, U14.6 (VSS), U14.11 (A0), U14.12 (A1), U14.13 (A2), U14.14 (~RESET), U14.29 (EP), U15.3 (com_a), U16.3 (com_a); also elsewhere on the board
unnamed: D3.2, R13.2
unnamed: D4.2, R14.2
unnamed: D5.2, R28.2
unnamed: D6.2, R30.2
unnamed: D7.2, R31.2
unnamed: D8.2, R32.2
